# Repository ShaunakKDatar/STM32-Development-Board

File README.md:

# STM32F1038TX Development Board

## Overview
This STM32F1038TX development board is designed for embedded system developers and hobbyists. It features essential peripherals and interfaces for rapid prototyping and testing. The board is powered by an AMS1117 voltage regulator, ensuring a stable 3.3V supply from USB input.

## Features
- **Microcontroller:** STM32F1038TX (ARM Cortex-M3)
- **Clock:** 16MHz External Crystal Oscillator
- **Voltage Regulator:** AMS1117 (USB to 3.3V conversion)
- **Connectors:**
   - UART
   - SWD (Serial Wire Debug)
   - I2C
- **Switches:**
   - User SPDT Switch
   - NRST (Reset) Switch
   - BOOT0 Switch
- **User LED:** 1 programmable user LED

## Pin Configuration
- **UART Pins:** TX (PA9), RX (PA10)
- **I2C Pins:** SDA (PB7), SCL (PB6)
- **SWD Pins:** SWCLK (PA14), SWDIO (PA13)
- **User LED:** PA5
- **SPDT Switch:** PA0
- **NRST Switch:** NRST Pin
- **BOOT0 Switch:** BOOT0 Pin

## Power Supply
- **Input Voltage:** 5V via USB
- **Regulated Voltage:** 3.3V via AMS1117

## Programming and Debugging
1. Use an SWD programmer (e.g., ST-Link V2) for flashing firmware.
2. Ensure BOOT0 is set to 0 for normal operation, 1 for DFU/bootloader mode.
3. Use UART for serial communication.

## Getting Started
1. Connect the board to your computer via USB.
2. Flash firmware using SWD.
3. Use UART for debugging and monitoring.
4. Toggle the User LED and interact with the SPDT switch.

## Safety Precautions
- Ensure correct power supply voltage.
- Avoid short circuits on the board.
- Handle components with care.

## Schematics

## PCB Routing

## 3D Model

## Resources
- [STM32F103 Reference Manual](https://www.st.com/resource/en/reference_manual/cd00171190.pdf)
- [STM32CubeIDE](https://www.st.com/en/development-tools/stm32cubeide.html)

## License
This project is open-source under the MIT License.

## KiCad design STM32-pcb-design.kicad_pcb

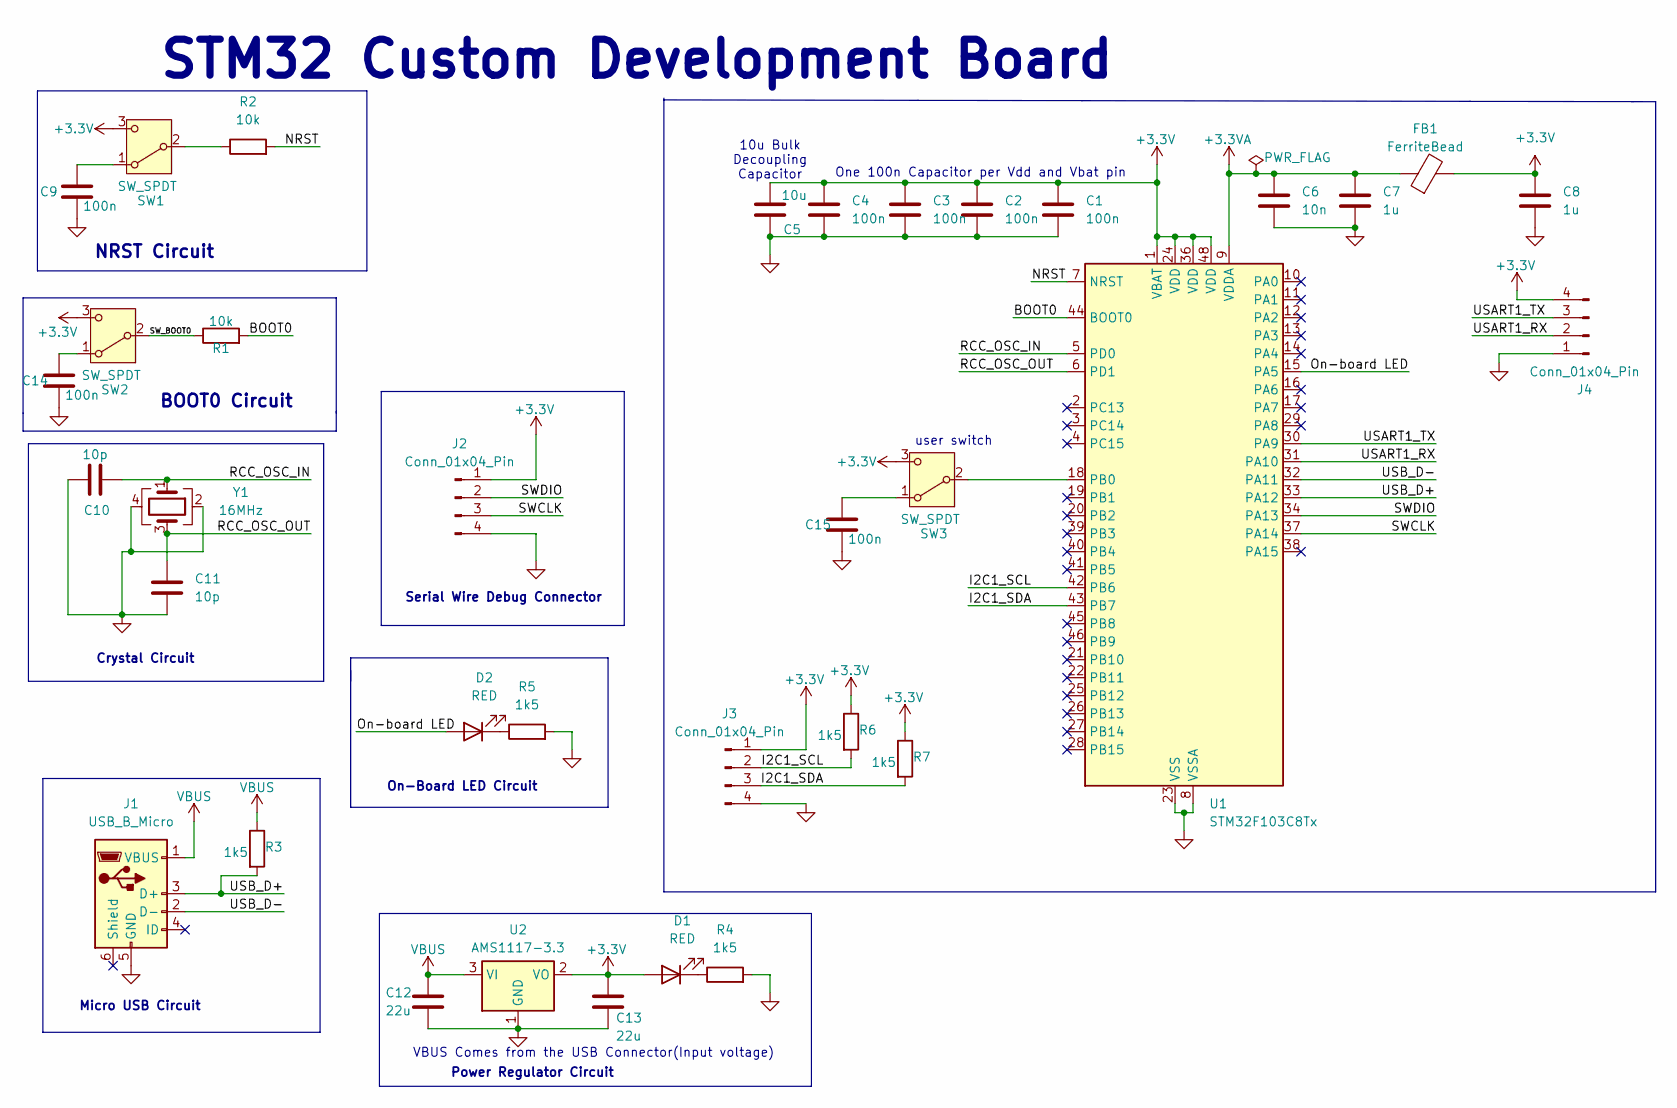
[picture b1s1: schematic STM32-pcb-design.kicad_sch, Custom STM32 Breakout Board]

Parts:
C1, C2, C3, C4, C9, C14, C15: 100n; C_0402_1005Metric
C5: 10u; C_0603_1608Metric
C6: 10n; C_0402_1005Metric
C7, C8: 1u; C_0402_1005Metric
C10, C11: 10p; C_0402_1005Metric
C12, C13: 22u; C_0603_1608Metric
D1, D2: RED; LED_0603_1608Metric
FB1: FerriteBead; L_0603_1608Metric
J1: USB_B_Micro; USB_Micro-B_Wuerth_629105150521
J2, J3, J4: Conn_01x04_Pin; PinHeader_1x04_P2.54mm_Vertical
R1, R2: 10k; R_0402_1005Metric
R3, R4, R5, R6, R7: 1k5; R_0402_1005Metric
SW1, SW2, SW3: SW_SPDT; SW_SPDT_PCM12
U1: STM32F103C8Tx; LQFP-48_7x7mm_P0.5mm
U2: AMS1117-3.3; SOT-223-3_TabPin2
Y1: 16MHz; Crystal_SMD_3225-4Pin_3.2x2.5mm

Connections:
+3.3V: C1.1, C2.1, C3.1, C4.1, C5.1, C8.1, C13.1, D1.2 (A), FB1.2, J2.1, J3.1, J4.4, R6.1, R7.1, SW1.3 (C), SW2.3 (C), SW3.3 (C), U1.1 (VBAT), U1.24 (VDD), U1.36 (VDD), U1.48 (VDD), U2.2 (VO)
+3.3VA: C6.1, C7.1, FB1.1, U1.9 (VDDA)
/BOOT0: R1.2, U1.44 (BOOT0)
/I2C1_SCL: J3.2, R6.2, U1.42 (PB6)
/I2C1_SDA: J3.3, R7.2, U1.43 (PB7)
/NRST: R2.2, U1.7 (NRST)
/On-board LED: D2.2 (A), U1.15 (PA5)
/RCC_OSC_IN: C10.2, U1.5 (PD0), Y1.1
/RCC_OSC_OUT: C11.1, U1.6 (PD1), Y1.3
/SWCLK: J2.3, U1.37 (PA14)
/SWDIO: J2.2, U1.34 (PA13)
/SW_BOOT0: R1.1, SW2.2 (B)
/USART1_RX: J4.2, U1.31 (PA10)
/USART1_TX: J4.3, U1.30 (PA9)
/USB_D+: J1.3 (D+), R3.2, U1.33 (PA12)
/USB_D-: J1.2 (D-), U1.32 (PA11)
GND: C1.2, C2.2, C3.2, C4.2, C5.2, C6.2, C7.2, C8.2, C9.2, C10.1, C11.2, C12.2, C13.2, C14.2, C15.2, J1.5 (GND), J2.4, J3.4, J4.1, R4.2, R5.2, U1.8 (VSSA), U1.23 (VSS), U1.35 (VSS), U1.47 (VSS), U2.1 (GND), Y1.2, Y1.4
unnamed: D1.1 (K), R4.1
unnamed: D2.1 (K), R5.1
unnamed: C9.1, SW1.1 (A)
unnamed: R2.1, SW1.2 (B)
unnamed: C14.1, SW2.1 (A)
unnamed: C15.1, SW3.1 (A)
unnamed: SW3.2 (B), U1.18 (PB0)
VBUS: C12.1, J1.1 (VBUS), R3.1, U2.3 (VI)

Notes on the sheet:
On-Board LED Circuit
10u Bulk Decoupling Capacitor
BOOT0 Circuit
Power Regulator Circuit
Crystal Circuit
One 100n Capacitor per Vdd and Vbat pin
Micro USB Circuit
Serial Wire Debug Connector
STM32 Custom Development Board
NRST Circuit
VBUS Comes from the USB Connector(Input voltage)
user switch

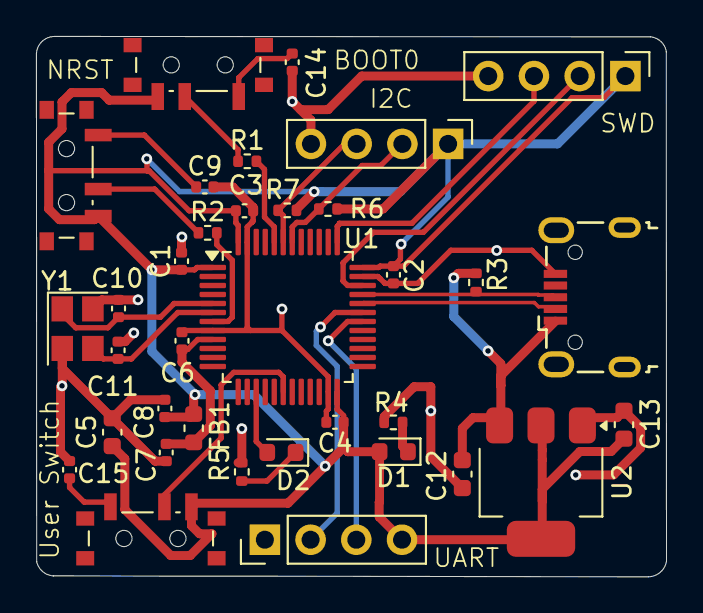
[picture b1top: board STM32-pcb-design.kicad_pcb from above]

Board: 2 copper layers, 35.0 x 30.0 mm, 35 parts (0 on the bottom side), 25 nets.

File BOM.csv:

"Reference","Value","Datasheet","Footprint","Qty","DNP"
"C1,C2,C3,C4,C9,C14,C15","100n","~","Capacitor_SMD:C_0402_1005Metric","7",""
"C5","10u","~","Capacitor_SMD:C_0603_1608Metric","1",""
"C6","10n","~","Capacitor_SMD:C_0402_1005Metric","1",""
"C7,C8","1u","~","Capacitor_SMD:C_0402_1005Metric","2",""
"C10,C11","10p","~","Capacitor_SMD:C_0402_1005Metric","2",""
"C12,C13","22u","~","Capacitor_SMD:C_0603_1608Metric","2",""
"D1,D2","RED","~","LED_SMD:LED_0603_1608Metric","2",""
"FB1","FerriteBead","~","Inductor_SMD:L_0603_1608Metric","1",""
"J1","USB_B_Micro","~","Connector_USB:USB_Micro-B_Wuerth_629105150521","1",""
"J2,J3,J4","Conn_01x04_Pin","~","Connector_PinHeader_2.54mm:PinHeader_1x04_P2.54mm_Vertical","3",""
"R1,R2","10k","~","Resistor_SMD:R_0402_1005Metric","2",""
"R3,R4,R5,R6,R7","1k5","~","Resistor_SMD:R_0402_1005Metric","5",""
"SW1,SW2,SW3","SW_SPDT","~","Button_Switch_SMD:SW_SPDT_PCM12","3",""
"U1","STM32F103C8Tx","https://www.st.com/resource/en/datasheet/stm32f103c8.pdf","Package_QFP:LQFP-48_7x7mm_P0.5mm","1",""
"U2","AMS1117-3.3","http://www.advanced-monolithic.com/pdf/ds1117.pdf","Package_TO_SOT_SMD:SOT-223-3_TabPin2","1",""
"Y1","16MHz","~","Crystal:Crystal_SMD_3225-4Pin_3.2x2.5mm","1",""

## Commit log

2024-12-24 Edited Text in Schematic
2024-12-24 Adds Routing Pictures to Readme
2024-12-24 Adds Schematic Pictures to Readme
2024-12-24 Adds Routing Pictures with back layer to Readme
2024-12-30 Changed the routing for the usb connector
2024-12-30 Update README.md with better routing images and 3d-model
2024-12-31 Re-oriented the AMS1117
2024-12-31 Moved the ams1117 to avoid soldering issues
2024-12-31 Moved the ams1117
2025-01-01 Changed Pull-up to vbus from 3.3V
